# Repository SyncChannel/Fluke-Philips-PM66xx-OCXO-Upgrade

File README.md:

# Fluke-Philips-PM66xx-OCXO-Upgrade

A custom OCXO upgrade board for the PM66xx line of frequency counters.

Read more about the design on my blog:

http://syncchannel.blogspot.com/2016/04/flukephilips-pm66xx-frequency-counter.html

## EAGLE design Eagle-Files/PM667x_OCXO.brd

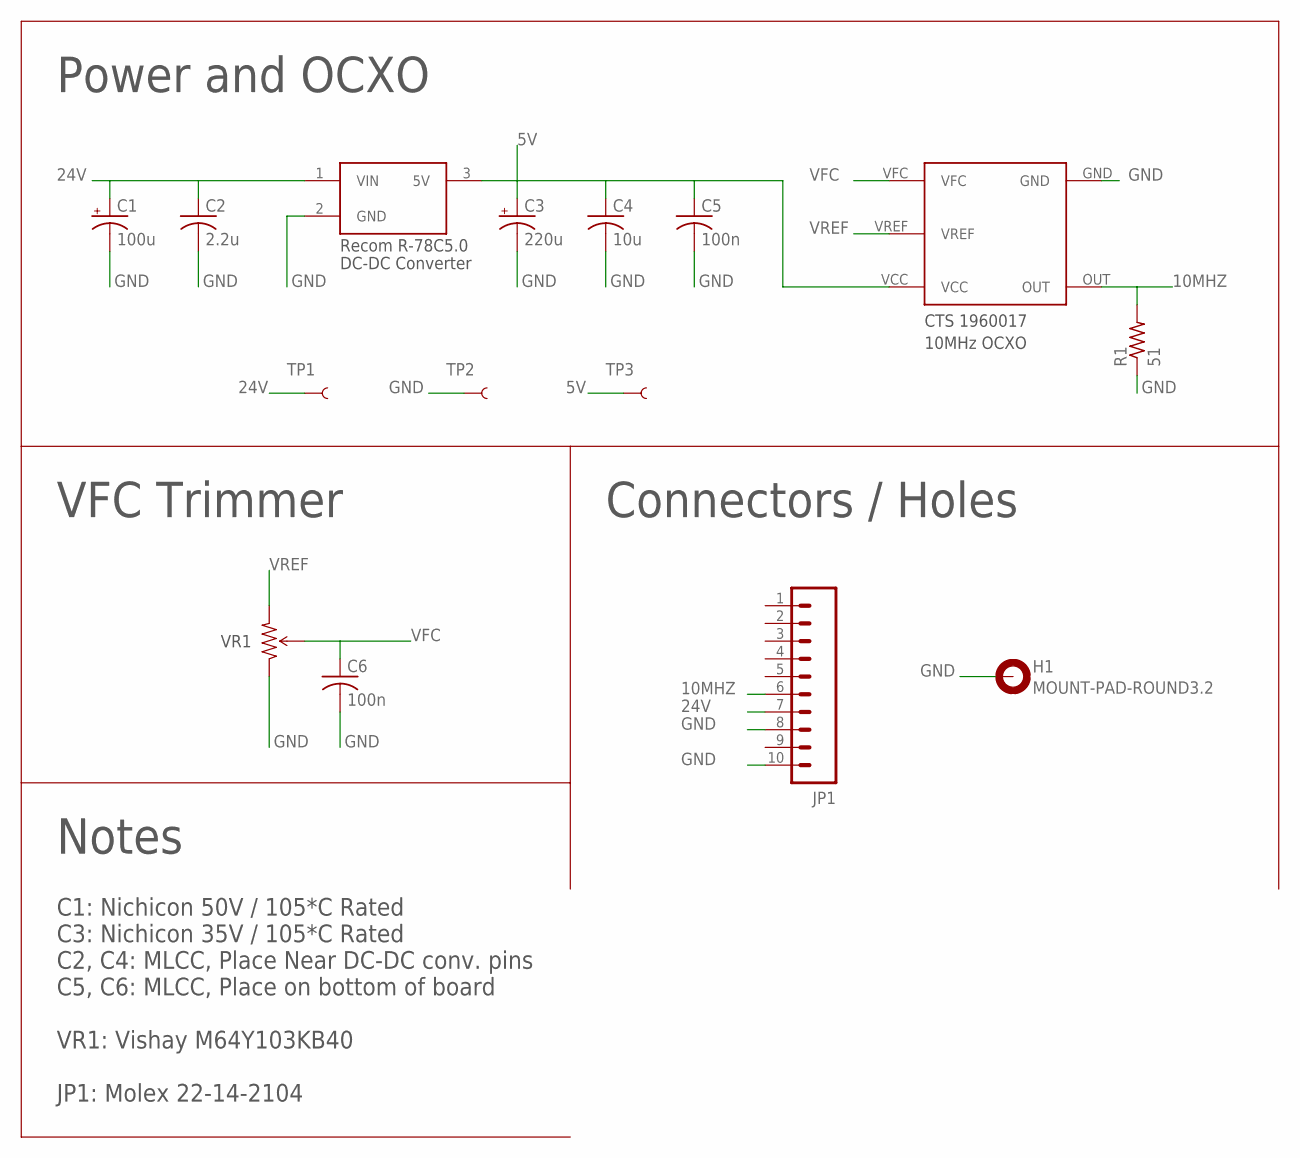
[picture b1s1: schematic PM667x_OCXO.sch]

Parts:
C1: 100u; E3,5-8
C2: 2.2u; C0805
C3: 220u; E3,5-8
C4: 10u; C0805
C5, C6: 100n; C0603
H1: MOUNT-PAD-ROUND3.2; 3,2-PAD
JP1: M10NO_SILK_PTH_FEMALE; 1X10_NO_SILK
R1: 51; R1206
TP1, TP2, TP3: TEST-POINT3X5; PAD.03X.05
U$1: CTS1960017
U$3: R-78C5.0
U$4: TE_CB10_TRIMMER; TE_CONNECTIVITY_CB10_TRIMMER

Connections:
5V: C3.+, C4.1, C5.1, TP3.P$1, U$1.VCC, U$3.3 (5V)
10MHZ: JP1.6, R1.2, U$1.OUT
24V: C1.+, C2.1, JP1.7, TP1.P$1, U$3.1 (VIN)
GND: C1.-, C2.2, C3.-, C4.2, C5.2, C6.2, H1.B3,2, JP1.8, JP1.10, R1.1, TP2.P$1, U$1.GND, U$3.2 (GND), U$4.A (CCW)
VFC: C6.1, U$1.VFC, U$4.B (WIPER)
VREF: U$1.VREF, U$4.C (CW)

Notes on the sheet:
VR1
CTS 1960017
Recom R-78C5.0
DC-DC Converter
10MHz OCXO
VFC Trimmer
Connectors / Holes
Power and OCXO
C1: Nichicon 50V / 105*C Rated C3: Nichicon 35V / 105*C Rated C2, C4: MLCC, Place Near DC-DC conv. pins C5, C6: MLCC, Place on bottom of board VR1: Vishay M64Y103KB40 JP1: Molex 22-14-2104
Notes

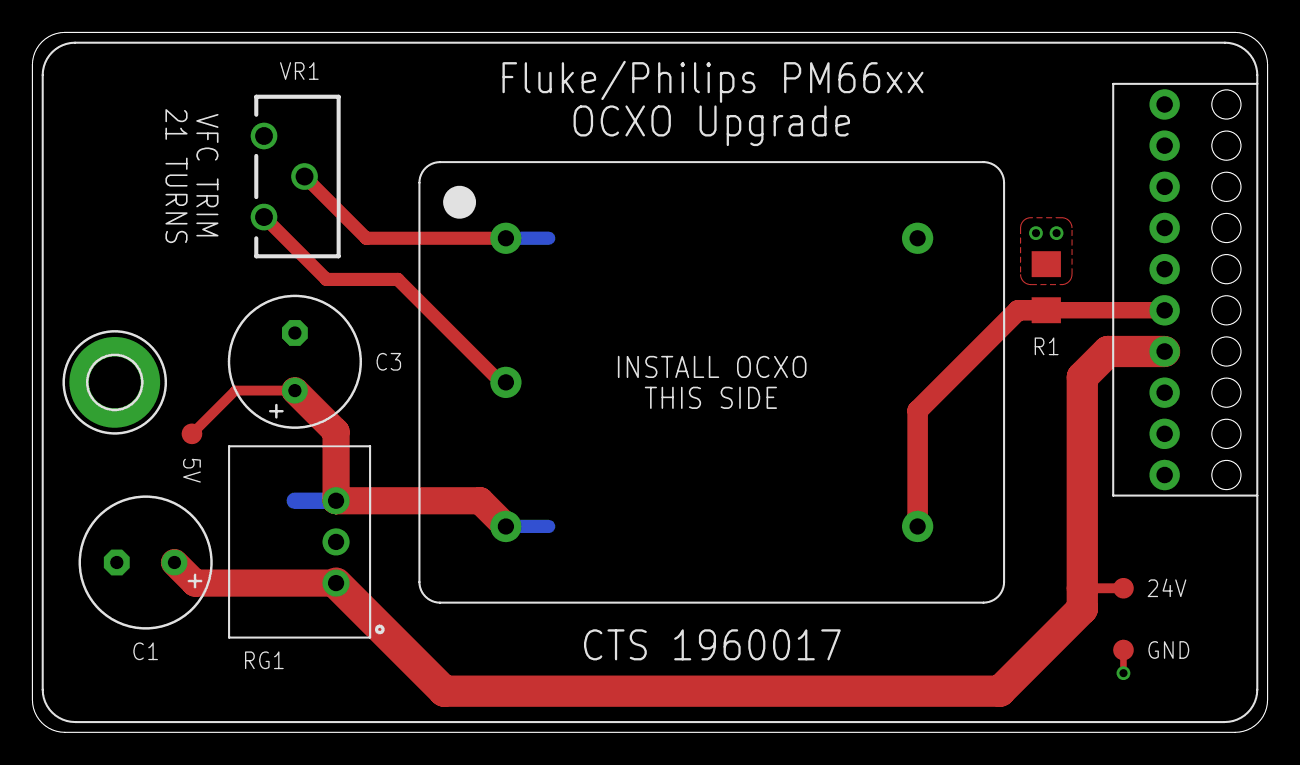
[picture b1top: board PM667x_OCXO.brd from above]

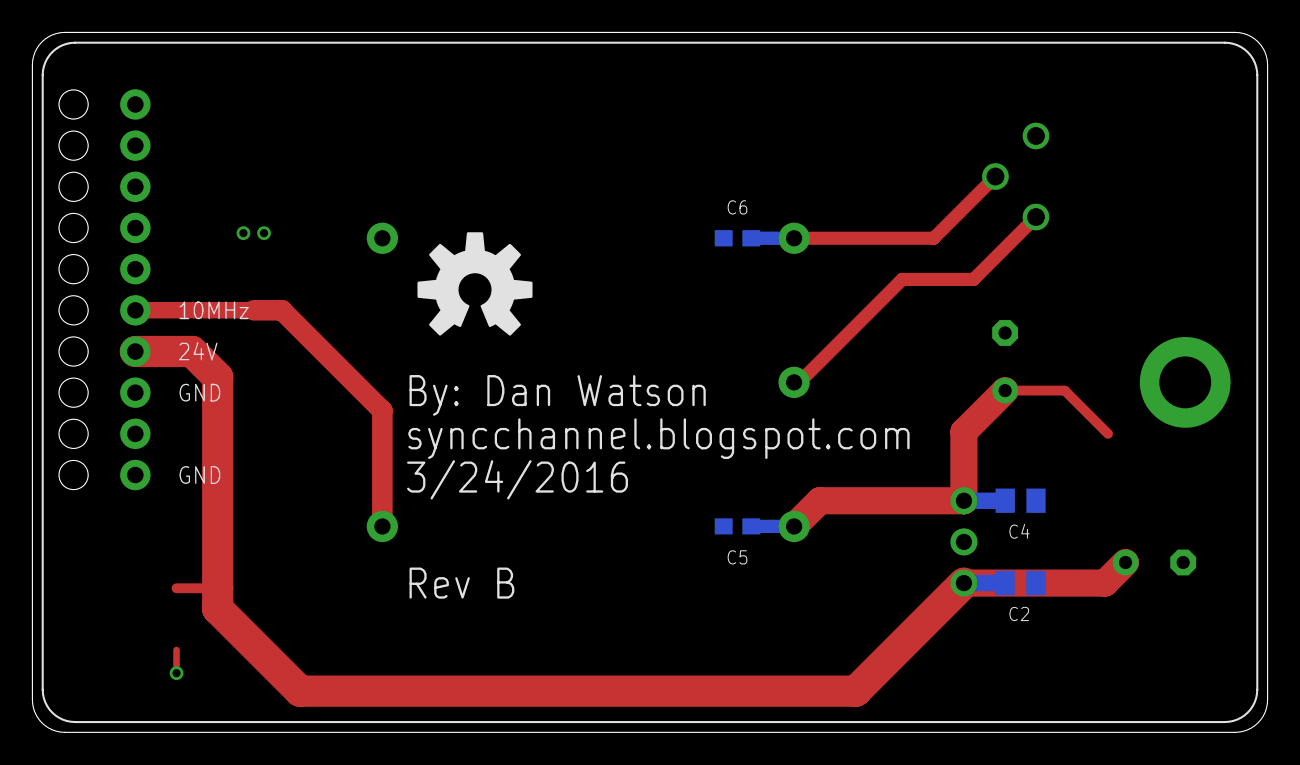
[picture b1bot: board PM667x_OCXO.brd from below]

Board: 2 copper layers, 76.2 x 43.2 mm, 16 parts (5 on the bottom side), 6 nets.

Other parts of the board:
U$2: OSHW-LOGO-L

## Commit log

2016-04-13 Added files via upload
    Upload board file
2016-04-13 Added files via upload
    Upload schematic file
2016-04-13 Update README.md
    Update readme

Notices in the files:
parts and their libraries:
SparkFun-Connectors: Licensing: Creative Commons ShareAlike 4.0 International - https://creativecommons.org/licenses/by-sa/4.0
